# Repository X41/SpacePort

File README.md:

# SpacePort
 An open source devboard for the Nintendo Switch 

This project is Licensed under CC BY-NC-SA 4.0
If you want to sell modified versions of this board, feel free to contact me

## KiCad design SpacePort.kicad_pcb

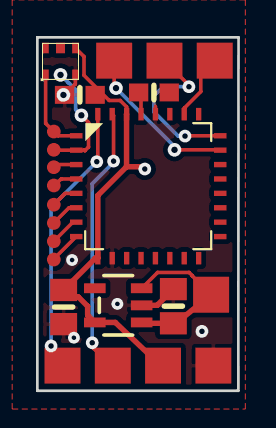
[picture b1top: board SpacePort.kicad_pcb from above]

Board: 2 copper layers, 11.2 x 19.6 mm, 23 parts (0 on the bottom side), 17 nets.

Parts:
C1, C8: 10uF; 0805-NO
C3, C4: 1uF; 0603-NO
TP1, TP11, TP12, TP13, TP14, TP15, TP16, TP17: TEST-POINT3; PAD.03X.03
TP2, TP3, TP4, TP5, TP6, TP7, TP8, TP9: TPSQTP20SQ; TP20SQ
U1: AP2112K-3.3; SOT23-5
U$1: ATSAMD21E18A-AU; 32-TQFP
U$3: APA1022020; APA102_2020

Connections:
3.3V: C4.1, C8.1, TP8.TP, U1.5, U$1.9, U$1.30, U$3.V_CC
/CI: TP11.P$1, U$1.2, U$3.C_IN
/D+: TP4.TP, U$1.24
/D-: TP5.TP, U$1.23
/DI: TP1.P$1, U$1.1, U$3.D_IN
/RST: TP9.TP, U$1.26
/SWC: TP7.TP, U$1.31
/SWD: TP6.TP, U$1.32
GND: C1.2, C3.2, C4.2, C8.2, TP2.TP, U1.2, U$1.10, U$1.28, U$3.GND
unnamed: C3.1, U$1.29
unnamed: TP12.P$1, U$1.3
unnamed: TP13.P$1, U$1.4
unnamed: TP14.P$1, U$1.5
unnamed: TP15.P$1, U$1.6
unnamed: TP16.P$1, U$1.7
unnamed: TP17.P$1, U$1.8
VBAT: C1.1, TP3.TP, U1.1, U1.3

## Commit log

2018-08-28 here come dat boi
2018-08-28 added license
2018-08-30 knew i'd forget something. now includes the parts lib. also fixed the linking
